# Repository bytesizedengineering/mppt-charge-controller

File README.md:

## License  
This project is licensed under the GNU General Public License v3.0 - see the [LICENSE](LICENSE) file for details.

# mppt charge controller
BQ 24650 datasheet can be found here https://www.ti.com/general/docs/suppproductinfo.tsp?distId=10&gotoUrl=https%3A%2F%2Fwww.ti.com%2Flit%2Fgpn%2Fbq24650

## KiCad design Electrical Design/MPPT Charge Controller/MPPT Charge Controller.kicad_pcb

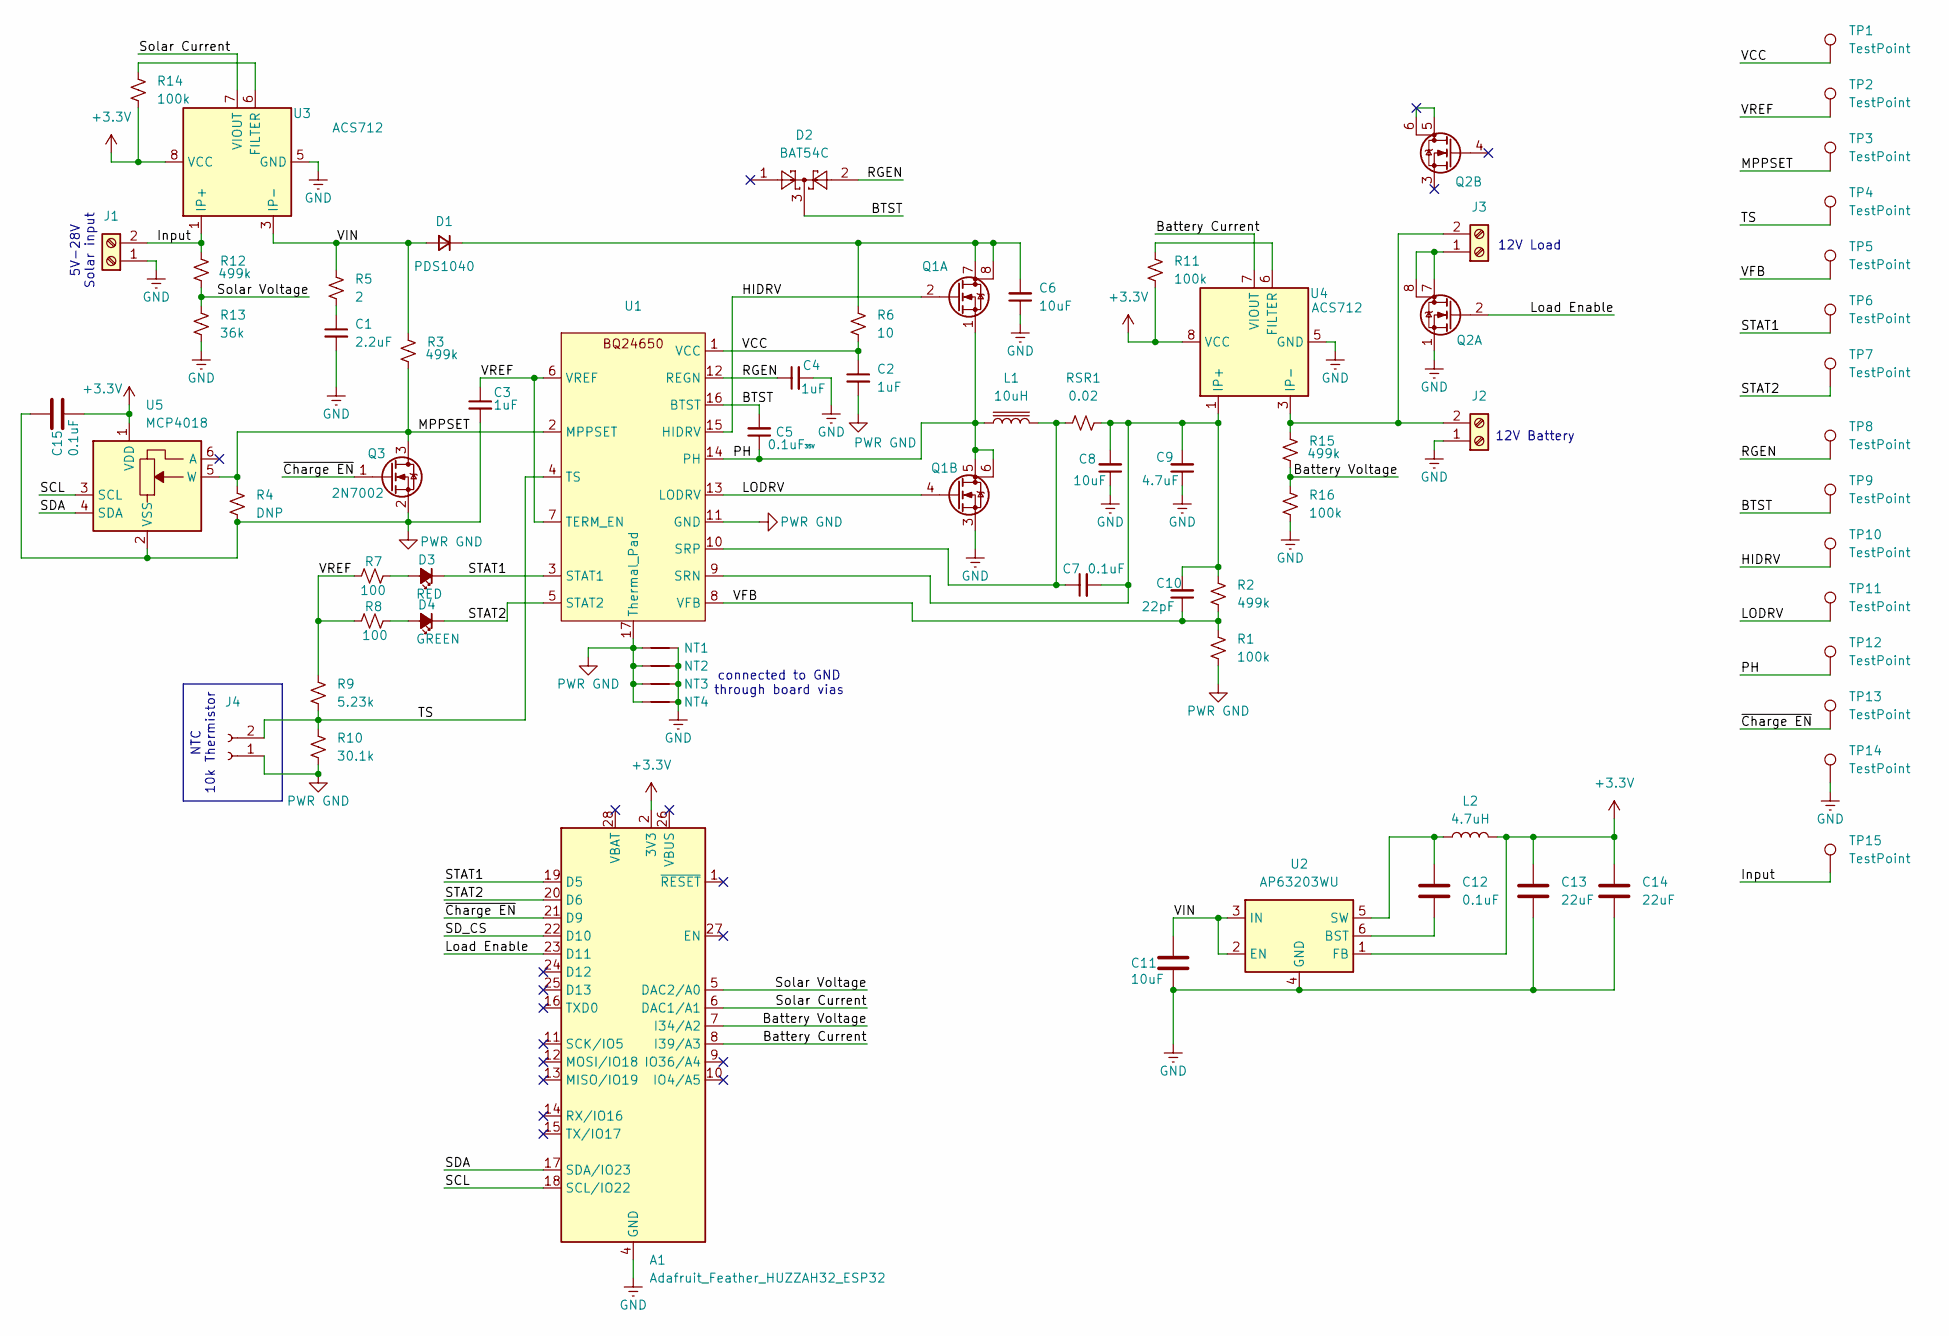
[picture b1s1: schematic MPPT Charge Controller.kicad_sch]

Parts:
A1: Adafruit_Feather_HUZZAH32_ESP32; Adafruit_Feather
C1: 2.2uF; C_1210_3225Metric
C2, C3, C4: 1uF; C_0603_1608Metric
C5: 0.1uF; C_0603_1608Metric; Voltage Rating 35V
C6, C8: 10uF; C_1206_3216Metric
C7, C12, C15: 0.1uF; C_0603_1608Metric
C9: 4.7uF; C_0805_2012Metric
C10: 22pF; C_0603_1608Metric
C11: 10uF; C_0603_1608Metric
C13, C14: 22uF; C_0603_1608Metric
D1: PDS1040; D_PowerDI-5
D2: BAT54C; SOT-23
D3: RED; LED_0603_1608Metric
D4: GREEN; LED_0603_1608Metric
J1, J2, J3: Conn_01x02_Socket; TerminalBlock_bornier-2_P5.08mm
J4: PinSocket_1x02_P2.54mm_Vertical
L1: 10uH; L_Vishay_6.9x6.5
L2: 4.7uH; L_Vishay_IFSC-1515AH_4x4x1.8mm
NT1, NT2, NT3, NT4: NetTie-2_SMD_Pad0.5mm
Q1, Q2: Q_Dual_NMOS_S1G1S2G2D2D2D1D1; PowerPAK_SO-8_Dual
Q3: 2N7002; SOT-23
R1, R11, R14, R16: 100k; R_0603_1608Metric
R2, R3, R12, R15: 499k; R_0603_1608Metric
R4: DNP; R_0603_1608Metric
R5: 2; R_2512_6332Metric
R6: 10; R_0603_1608Metric
R7, R8: 100; R_0603_1608Metric
R9: 5.23k; R_0603_1608Metric
R10: 30.1k; R_0603_1608Metric
R13: 36k; R_0603_1608Metric
RSR1: 0.02; R_1206_3216Metric
TP1, TP2, TP3, TP4, TP5, TP6, TP7, TP8, TP9, TP10, TP11, TP12, TP13: TestPoint; TestPoint_Pad_D1.0mm
TP14, TP15: TestPoint; TestPoint_Loop_D2.60mm_Drill1.6mm_Beaded
U1: VQFN-16_EP_3.5x3.5_Pitch0.5mm
U2: AP63203WU; TSOT-23-6
U3, U4: ACS712; SOIC-8_3.9x4.9mm_P1.27mm
U5: MCP4018; SOT-363_SC-70-6

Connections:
+3.3V: A1.2 (3V3), C13.1, C14.1, C15.1, L2.2, R11.2, R14.2, U2.1 (FB), U3.8 (VCC), U4.8 (VCC), U5.1 (VDD)
/BTST: C5.2, D2.3, TP9.1, U1.16 (BTST)
/Battery Current: A1.8 (I39/A3), U4.7 (VIOUT)
/Battery Voltage: A1.7 (I34/A2), R15.2, R16.1
/HIDRV: Q1.2 (G), TP10.1, U1.15 (HIDRV)
/Input: J1.2, R12.1, TP15.1, U3.1 (IP+), U3.2 (IP+)
/LODRV: Q1.4 (G), TP11.1, U1.13 (LODRV)
/Load Enable: A1.23 (D11), Q2.2 (G)
/MPPSET: Q3.3 (D), R3.2, R4.1, TP3.1, U1.2 (MPPSET), U5.5 (W)
/PH: C5.1, L1.1, Q1.1 (S), Q1.5 (D), Q1.6 (D), TP12.1, U1.14 (PH)
/RGEN: C4.1, D2.2, TP8.1, U1.12 (REGN)
/SCL: A1.18 (SCL/IO22), U5.3 (SCL)
/SDA: A1.17 (SDA/IO23), U5.4 (SDA)
/SD_CS: A1.22 (D10)
/STAT1: A1.19 (D5), D3.1 (K), TP6.1, U1.3 (STAT1)
/STAT2: A1.20 (D6), D4.1 (K), TP7.1, U1.5 (STAT2)
/Solar Current: A1.6 (DAC1/A1), U3.7 (VIOUT)
/Solar Voltage: A1.5 (DAC2/A0), R12.2, R13.1
/TS: J4.2, R9.2, R10.1, TP4.1, U1.4 (TS)
/VCC: C2.1, R6.2, TP1.1, U1.1 (VCC)
/VFB: C10.1, R1.1, R2.2, TP5.1, U1.8 (VFB)
/VIN: C11.2, D1.2 (A), R3.1, R5.1, U2.2 (EN), U2.3 (IN), U3.3 (IP-), U3.4 (IP-)
/VREF: C3.1, R7.1, R8.1, R9.1, TP2.1, U1.6 (VREF), U1.7 (TERM_EN)
/~Charge EN: A1.21 (D9), Q3.1 (G), TP13.1
GND: A1.4 (GND), C1.2, C4.2, C6.1, C8.1, C9.1, C11.1, C13.2, C14.2, J1.1, J2.1, NT1.2, NT2.2, NT3.2, NT4.2, Q1.3 (S), Q2.1 (S), R13.2, R16.2, TP14.1, U2.4 (GND), U3.5 (GND), U4.5 (GND)
unnamed: C1.1, R5.2
unnamed: C6.2, D1.1 (K), Q1.7 (D), Q1.8 (D), R6.1
unnamed: D3.2 (A), R7.2
unnamed: D4.2 (A), R8.2
unnamed: J2.2, J3.2, R15.1, U4.3 (IP-), U4.4 (IP-)
unnamed: J3.1, Q2.7 (D), Q2.8 (D)
unnamed: C7.2, C8.2, C9.2, C10.2, R2.1, RSR1.1, U1.9 (SRN), U4.1 (IP+), U4.2 (IP+)
unnamed: C7.1, L1.2, RSR1.2, U1.10 (SRP)
unnamed: C12.2, U2.6 (BST)
unnamed: C12.1, L2.1, U2.5 (SW)
unnamed: R14.1, U3.6 (FILTER)
unnamed: R11.1, U4.6 (FILTER)
PWR GND: C2.2, C3.2, C15.2, J4.1, NT1.1, NT2.1, NT3.1, NT4.1, Q3.2 (S), R1.2, R4.2, R10.2, U1.11 (GND), U1.17 (Thermal_Pad), U5.2 (VSS)

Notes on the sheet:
NTC 10k Thermistor
5V-28V Solar input
12V Load
12V Battery
connected to GND through board vias

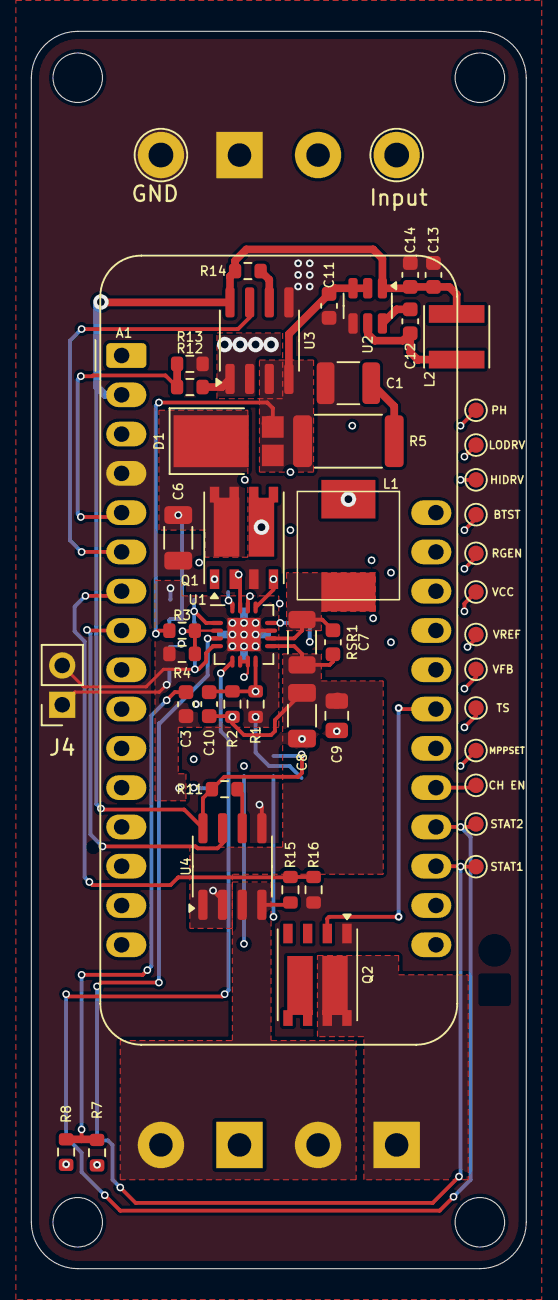
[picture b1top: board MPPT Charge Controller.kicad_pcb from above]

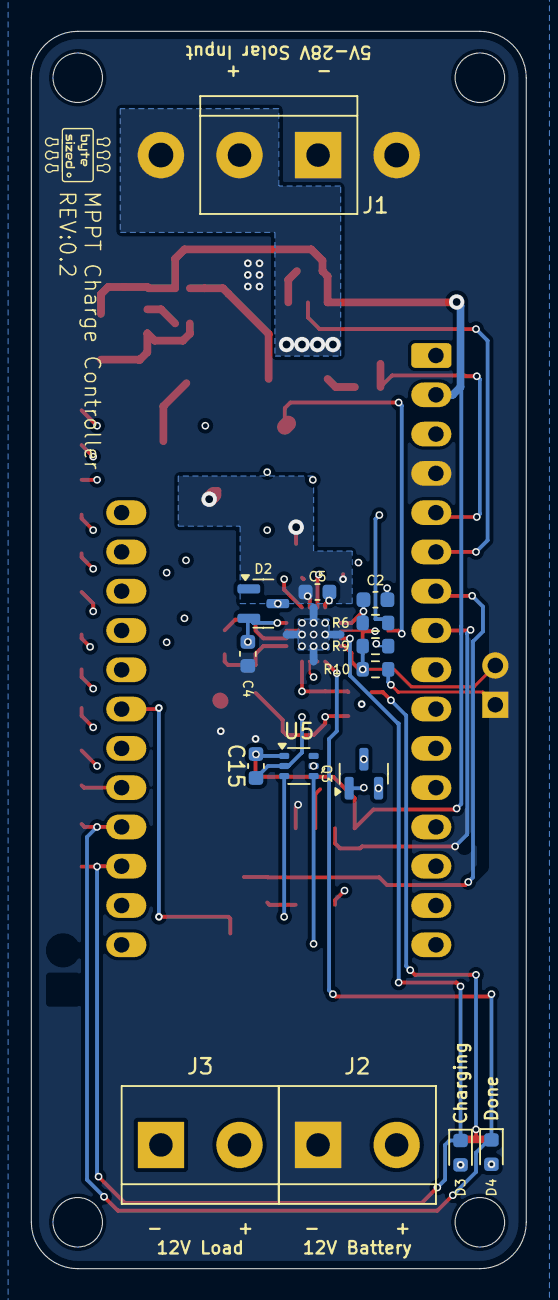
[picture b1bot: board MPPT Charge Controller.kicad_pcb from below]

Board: 4 copper layers, 32.0 x 80.0 mm, 70 parts (19 on the bottom side), 37 nets.

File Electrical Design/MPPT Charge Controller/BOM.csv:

"Reference","Value","Datasheet","Footprint","Qty","DNP"
"A1","Adafruit_Feather_HUZZAH32_ESP32","https://cdn-learn.adafruit.com/downloads/pdf/adafruit-huzzah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","Module:Adafruit_Feather","1",""
"C1","2.2uF","~","Capacitor_SMD:C_1210_3225Metric","1",""
"C2,C3,C4","1uF","~","Capacitor_SMD:C_0603_1608Metric","3",""
"C5,C7,C12,C15","0.1uF","~","Capacitor_SMD:C_0603_1608Metric","4",""
"C6,C8,C11","10uF","~","-- mixed values --","3",""
"C9","4.7uF","~","Capacitor_SMD:C_0805_2012Metric","1",""
"C10","22pF","~","Capacitor_SMD:C_0603_1608Metric","1",""
"C13,C14","22uF","~","Capacitor_SMD:C_0603_1608Metric","2",""
"D1","PDS1040","~","Diode_SMD:D_PowerDI-5","1",""
"D2","BAT54C","http://www.diodes.com/_files/datasheets/ds11005.pdf","Package_TO_SOT_SMD:SOT-23","1",""
"D3","RED","~","LED_SMD:LED_0603_1608Metric","1",""
"D4","GREEN","~","LED_SMD:LED_0603_1608Metric","1",""
"J1,J2,J3","Conn_01x02_Socket","~","TerminalBlock:TerminalBlock_bornier-2_P5.08mm","3",""
"L1","10uH","~","MPPT Charge Controller Footprint Library:L_Vishay_6.9x6.5","1",""
"L2","4.7uH","IFSC1515AHER4R7M01","Inductor_SMD:L_Vishay_IFSC-1515AH_4x4x1.8mm","1",""
"Q1,Q2","Q_Dual_NMOS_S1G1S2G2D2D2D1D1","~","Package_SO:PowerPAK_SO-8_Dual","2",""
"Q3","2N7002","https://www.onsemi.com/pub/Collateral/NDS7002A-D.PDF","Package_TO_SOT_SMD:SOT-23","1",""
"R1,R11,R14","100k","~","Resistor_SMD:R_0603_1608Metric","3",""
"R2,R3,R12,R15","499k","~","Resistor_SMD:R_0603_1608Metric","4",""
"R5","2","~","Resistor_SMD:R_2512_6332Metric","1",""
"R6","10","~","Resistor_SMD:R_0603_1608Metric","1",""
"R7,R8","10k","~","Resistor_SMD:R_0603_1608Metric","2",""
"R9","5.23k","~","Resistor_SMD:R_0603_1608Metric","1",""
"R10","30.1k","~","Resistor_SMD:R_0603_1608Metric","1",""
"R13","68k","~","Resistor_SMD:R_0603_1608Metric","1",""
"R16","150k","~","Resistor_SMD:R_0603_1608Metric","1",""
"RSR1","0.02","~","Resistor_SMD:R_1206_3216Metric","1",""
"TP1,TP2,TP3,TP4,TP5,TP6,TP7,TP8,TP9,TP10,TP11,TP12,TP13,TP14,TP15","TestPoint","~","-- mixed values --","15",""
"U1","~","","MPPT Charge Controller Footprint Library:VQFN-16_EP_3.5x3.5_Pitch0.5mm","1",""
"U2","AP63203WU","https://www.diodes.com/assets/Datasheets/AP63200-AP63201-AP6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","Package_TO_SOT_SMD:TSOT-23-6","1",""
"U3","ACS712xLCTR-05B","http://www.allegromicro.com/~/media/Files/Datasheets/ACS712-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","Package_SO:SOIC-8_3.9x4.9mm_P1.27mm","1",""
"U4","ACS712","http://www.allegromicro.com/~/media/Files/Datasheets/ACS712-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","Package_SO:SOIC-8_3.9x4.9mm_P1.27mm","1",""
"U5","MCP4018","http://ww1.microchip.com/downloads/en/DeviceDoc/22147a.pdf","Package_TO_SOT_SMD:SOT-363_SC-70-6","1",""

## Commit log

2024-04-19 Created KiCad project
2024-05-01 Created BQ24650 symbol and footprint
2024-05-09 Added circuitry to schematic
2024-05-28 Rev .01
2024-07-08 fixed R4 inconsistency
2024-07-26 Added battery temp thermistor connector
    Also cleaned up directory and added .gitignore
2024-07-26 renamed and cleaned up folders
2024-07-26 removed test firmware
2024-07-26 added test firmware to git ignore
2024-07-26 cleaned up file structure
2025-02-14 Update and rename LICENSE.txt to LICENSE
